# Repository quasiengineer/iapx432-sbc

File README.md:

# System board for Intel APX 432 GDP
FPGA-based single board computer to run iAPX 432 GDP

## Board

Full schematics in [pdf format](./images/schematic.pdf)

Here is shown only FPGA part of the board:

Archive with gerber files and drill locations could be found [here](./pcb/manufacturing.zip)

Bill of material in [CSV format](./pcb/bom.csv)

| Reference                                                                                                                                                                      | Qty | Value                   | Mouser Part Number   |
|---|---|---|---|
| Y1                                                                                                                                                                             | 1   | 250Mhz                  | 972-XLH536250000000I |
| U1                                                                                                                                                                             | 1   | SRAM                    | 870-61LPS12836A5TQL  |
| U2                                                                                                                                                                             | 1   | ICE40                   | 842-ICE40HX4K-TQ144  |
| FB1                                                                                                                                                                            | 1   | Ferrite_Bead            | 81-BLM18BD152SH1D    |
| D1                                                                                                                                                                             | 1   | Red                     | 710-150080RS75000    |
| D3,D4                                                                                                                                                                          | 2   | Green                   | 710-150080GS75000    |
| J1                                                                                                                                                                             | 1   | Type-C                  | 656-DX07S016JA1R1500 |
| L1                                                                                                                                                                             | 1   | 1u5, 5A                 | 652-SRP6530A-1R5M    |
| L2,L3                                                                                                                                                                          | 2   | 0u68, 5.5A              | 652-SRP2512-R68M     |
| J3                                                                                                                                                                             | 1   | Power                   | 649-67997-200HLF     |
| J2                                                                                                                                                                             | 1   | FPGA programming / UART | 649-1012938190604BLF |
| SW1                                                                                                                                                                            | 1   | FPGA Reset              | 640-SWT0010015016SSA |
| Q1                                                                                                                                                                             | 1   | MMBT3904                | 637-MMBT3904         |
| D2                                                                                                                                                                             | 1   | 1N5819                  | 621-1N5819HW-F       |
| R11,R12,R13,R14,R19                                                                                                                                                            | 5   | 100k                    | 603-RT0805DRE07100KL |
| R23                                                                                                                                                                            | 1   | 470R                    | 603-RT0805BRD07470RL |
| R21,R22                                                                                                                                                                        | 2   | 5k1                     | 603-RC0805FR-075K1L  |
| R2,R18                                                                                                                                                                         | 2   | 4k7                     | 603-RC0805FR-074K7L  |
| R16                                                                                                                                                                            | 1   | 34k8                    | 603-RC0805FR-0734K8L |
| R17,R20                                                                                                                                                                        | 2   | 2k2                     | 603-RC0805FR-072K2L  |
| R15                                                                                                                                                                            | 1   | 158k                    | 603-RC0805FR-07158KL |
| R1                                                                                                                                                                             | 1   | 22R                     | 603-RC0805FR-1322RL  |
| C43                                                                                                                                                                            | 1   | 33p                     | 603-CC805KRNPO9BN330 |
| C42                                                                                                                                                                            | 1   | 22p                     | 603-CC805JRNPO9BN220 |
| R9,R10                                                                                                                                                                         | 2   | 10                      | 603-AF0805FR-0710RL  |
| R4,R5,R8                                                                                                                                                                       | 3   | 100R                    | 603-AC0805FR-13100RL |
| R3,R6,R7                                                                                                                                                                       | 3   | 10k                     | 603-AA0805FR-0710KL  |
| U6                                                                                                                                                                             | 1   | TPS63002                | 595-TPS63002DRCR     |
| IC3                                                                                                                                                                            | 1   | Control signals         | 595-LVC16T245DGVRG4  |
| IC1                                                                                                                                                                            | 1   | Address/data bus        | 595-LVC16T245DGVRG4  |
| U4,U5                                                                                                                                                                          | 2   | LX7167ACLD-TR           | 494-LX7167ACLD-TR    |
| U3                                                                                                                                                                             | 1   | Bitstream flash         | 454-W25Q16JVSSIQ     |
| C38,C39,C46,C47                                                                                                                                                                | 4   | 1u                      | 187-CL21B105KPFNNNE  |
| C29,C30,C32,C33,C44,C45                                                                                                                                                        | 6   | 22u                     | 187-CL21A226MAYNNNE  |
| C34,C40,C41                                                                                                                                                                    | 3   | 10u                     | 187-CL21A106KQFNNNG  |
| C1..C19,C21,C22,C23,C25..C28,C31,C35,C36,C37,C50..C65 | 46  | 100n                    | 187-CL10B104KB8NNNC  |
| U8                                                                                                                                                                             | 1   | 43202                   |                      |
| U7                                                                                                                                                                             | 1   | 43201                   |                      |

## FPGA bitstream

Here is compiled [bitsream](./gateware/build/iapx432-sbc.bin).
You can flash it to memory chip via SPI programmer (there is 6-pin header for that).

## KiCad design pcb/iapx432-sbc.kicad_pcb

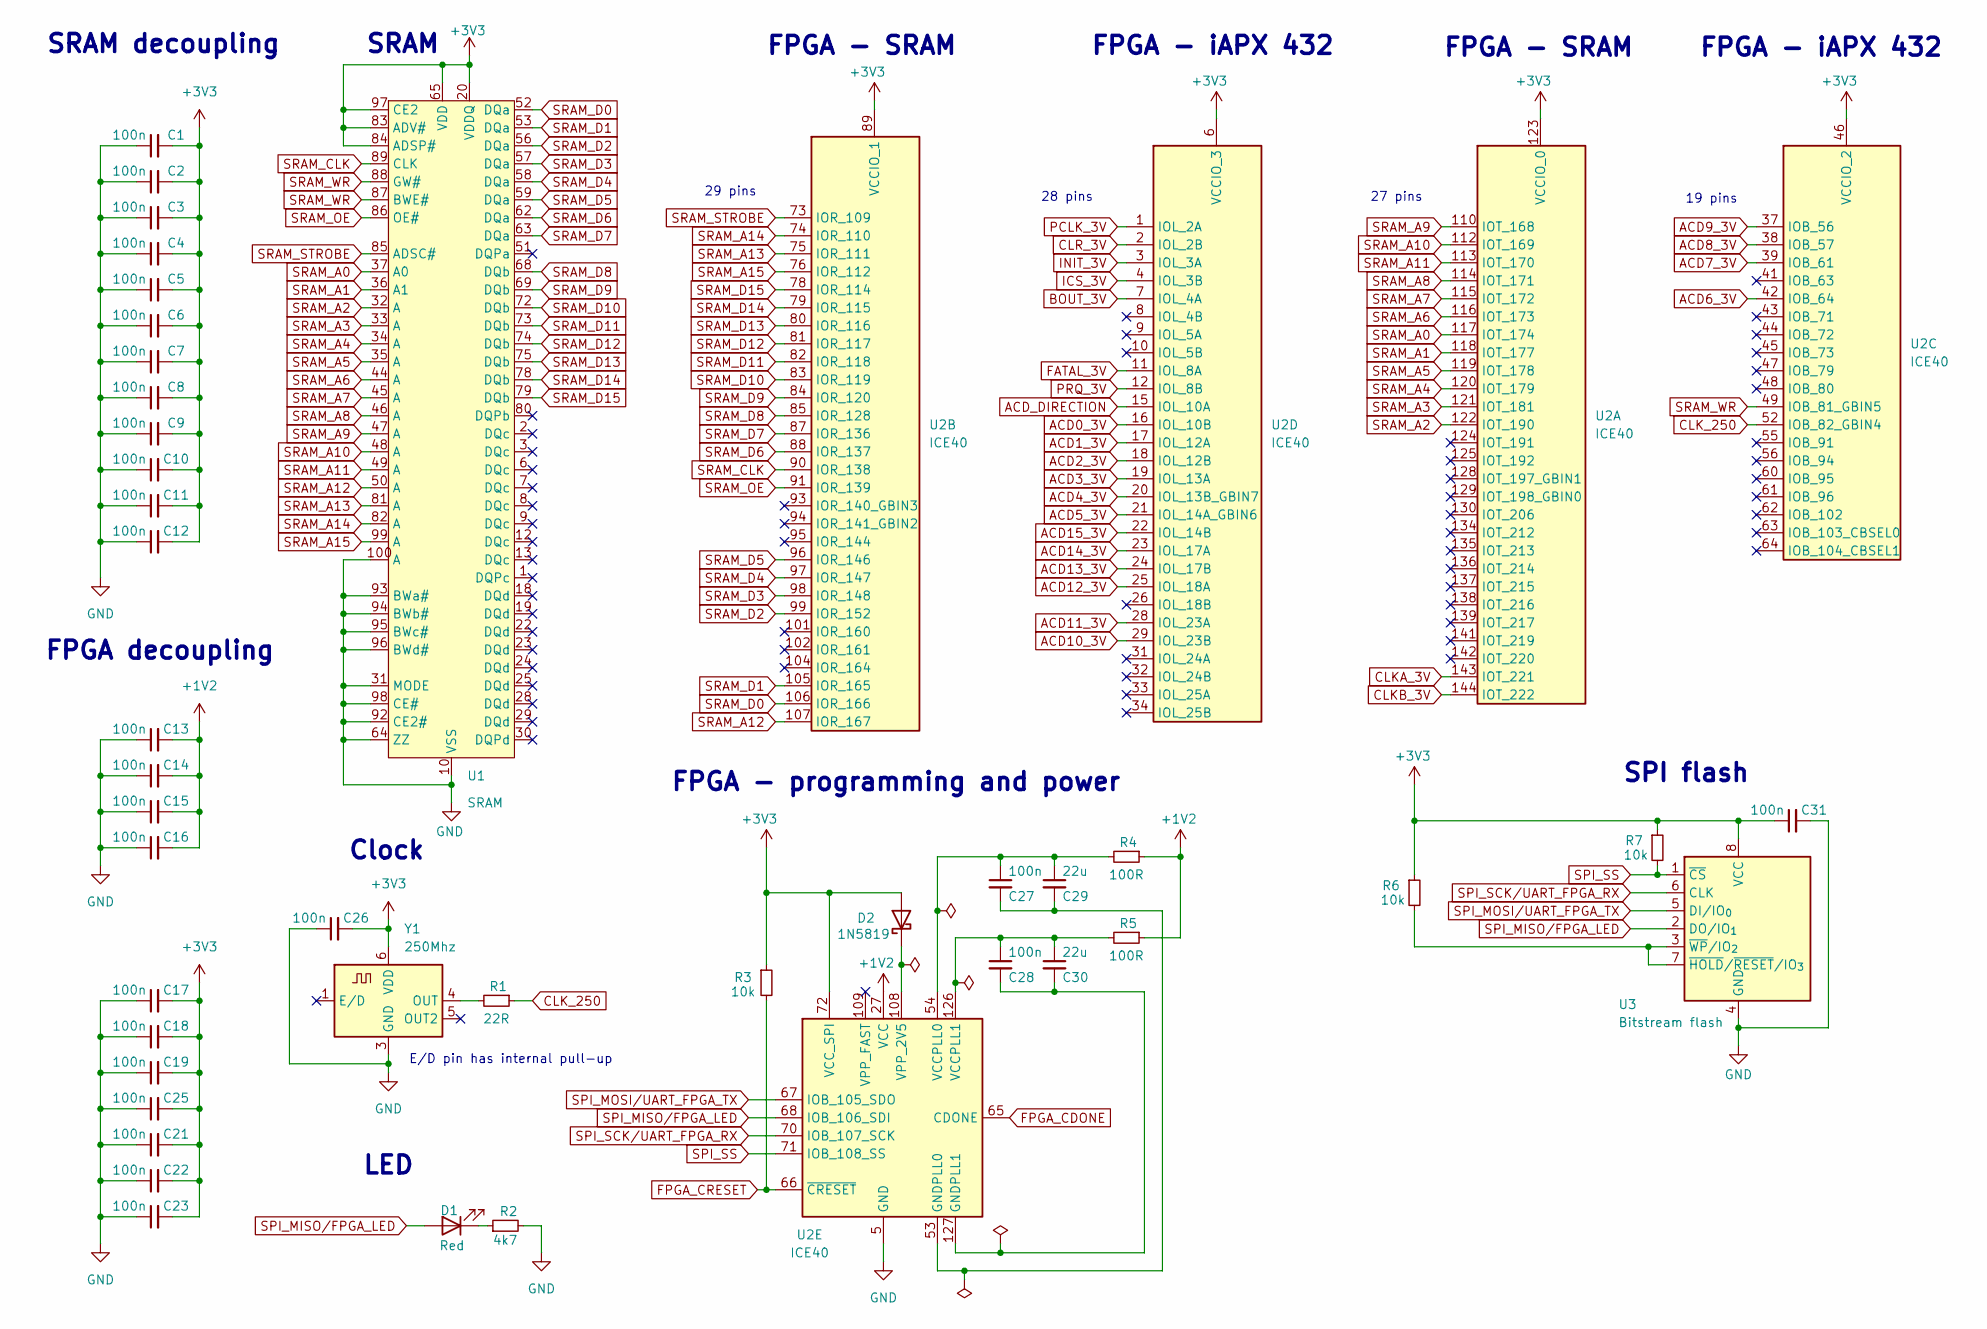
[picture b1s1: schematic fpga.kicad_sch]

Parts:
C1, C2, C3, C4, C5, C6, C7, C8, C9, C10, C11, C12, C13, C14, C15, C16, C17, C18, C19, C21, C22, C23, C25, C26, C27, C28, C31: 100n; C_0603_1608Metric_Pad1.08x0.95mm_HandSolder; Mouser Part Number 187-CL10B104KB8NNNC
C29, C30: 22u; C_0805_2012Metric_Pad1.18x1.45mm_HandSolder; Mouser Part Number 187-CL21A226MAYNNNE
D1: Red; LED_0805_2012Metric_Pad1.15x1.40mm_HandSolder; Mouser Part Number 710-150080RS75000
D2: 1N5819; D_SOD-123; Mouser Part Number 621-1N5819HW-F
R1: 22R; R_0805_2012Metric_Pad1.20x1.40mm_HandSolder; Mouser Part Number 603-RC0805FR-1322RL
R2: 4k7; R_0805_2012Metric_Pad1.20x1.40mm_HandSolder; Mouser Part Number 603-RC0805FR-074K7L
R3, R6, R7: 10k; R_0805_2012Metric_Pad1.20x1.40mm_HandSolder; Mouser Part Number 603-AA0805FR-0710KL
R4, R5: 100R; R_0805_2012Metric_Pad1.20x1.40mm_HandSolder; Mouser Part Number 603-AC0805FR-13100RL
U1: SRAM; PQFP-100_14x20mm_P0.65mm; Mouser Part Number 870-61LPS12836A5TQL
U2: ICE40; TQFP-144_20x20mm_P0.5mm; Mouser Part Number 842-ICE40HX4K-TQ144
U3: Bitstream flash; SOIC-8_5.3x5.3mm_P1.27mm; Mouser Part Number 454-W25Q16JVSSIQ
Y1: 250Mhz; XLH536250.000000I; Mouser Part Number 972-XLH536250000000I

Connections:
+1V2: C13.2, C14.2, C15.2, C16.2, R4.1, R5.1, U2.27 (VCC), U2.40 (VCC), U2.92 (VCC), U2.111 (VCC); also elsewhere on the board
+3V3: C1.2, C2.2, C3.2, C4.2, C5.2, C6.2, C7.2, C8.2, C9.2, C10.2, C11.2, C12.2, C17.2, C18.2, C19.2, C21.2, C22.2, C23.2, C25.2, C26.2, C31.1, D2.2 (A), R3.1, R6.1, R7.1, U1.4 (VDDQ), U1.11 (VDDQ), U1.15 (VDD), U1.20 (VDDQ), U1.27 (VDDQ), U1.41 (VDD), U1.54 (VDDQ), U1.61 (VDDQ), U1.65 (VDD), U1.70 (VDDQ), U1.77 (VDDQ), U1.83 (ADV#), U1.84 (ADSP#), U1.91 (VDD), U1.97 (CE2), U2.6 (VCCIO_3), U2.30 (VCCIO_3), U2.46 (VCCIO_2), U2.57 (VCCIO_2), U2.72 (VCC_SPI), U2.89 (VCCIO_1), U2.100 (VCCIO_1), U2.123 (VCCIO_0), U2.131 (VCCIO_0), U3.8 (VCC), Y1.6 (VDD); also elsewhere on the board
ACD0_3V: U2.16 (IOL_10B); also elsewhere on the board
ACD1_3V: U2.17 (IOL_12A); also elsewhere on the board
ACD2_3V: U2.18 (IOL_12B); also elsewhere on the board
ACD3_3V: U2.19 (IOL_13A); also elsewhere on the board
ACD4_3V: U2.20 (IOL_13B_GBIN7); also elsewhere on the board
ACD5_3V: U2.21 (IOL_14A_GBIN6); also elsewhere on the board
ACD6_3V: U2.42 (IOB_64); also elsewhere on the board
ACD7_3V: U2.39 (IOB_61); also elsewhere on the board
ACD8_3V: U2.38 (IOB_57); also elsewhere on the board
ACD9_3V: U2.37 (IOB_56); also elsewhere on the board
ACD10_3V: U2.29 (IOL_23B); also elsewhere on the board
ACD11_3V: U2.28 (IOL_23A); also elsewhere on the board
ACD12_3V: U2.25 (IOL_18A); also elsewhere on the board
ACD13_3V: U2.24 (IOL_17B); also elsewhere on the board
ACD14_3V: U2.23 (IOL_17A); also elsewhere on the board
ACD15_3V: U2.22 (IOL_14B); also elsewhere on the board
ACD_DIRECTION: U2.15 (IOL_10A); also elsewhere on the board
BOUT_3V: U2.7 (IOL_4A); also elsewhere on the board
CLKA_3V: U2.143 (IOT_221); also elsewhere on the board
CLKB_3V: U2.144 (IOT_222); also elsewhere on the board
CLK_250: R1.1, U2.52 (IOB_82_GBIN4)
CLR_3V: U2.2 (IOL_2B); also elsewhere on the board
FATAL_3V: U2.11 (IOL_8A); also elsewhere on the board
FPGA_CDONE: U2.65 (CDONE); also elsewhere on the board
FPGA_CRESET: R3.2, U2.66 (~CRESET); also elsewhere on the board
GND: C1.1, C2.1, C3.1, C4.1, C5.1, C6.1, C7.1, C8.1, C9.1, C10.1, C11.1, C12.1, C13.1, C14.1, C15.1, C16.1, C17.1, C18.1, C19.1, C21.1, C22.1, C23.1, C25.1, C26.1, C31.2, R2.2, U1.5 (VSS), U1.10 (VSS), U1.17 (VSS), U1.21 (VSS), U1.26 (VSS), U1.31 (MODE), U1.40 (VSS), U1.55 (VSS), U1.60 (VSS), U1.64 (ZZ), U1.67 (VSS), U1.71 (VSS), U1.76 (VSS), U1.90 (VSS), U1.92 (CE2#), U1.93 (BWa#), U1.94 (BWb#), U1.95 (BWc#), U1.96 (BWd#), U1.98 (CE#), U1.100 (A), U2.5 (GND), U2.13 (GND), U2.14 (GND), U2.59 (GND), U2.69 (GND), U2.86 (GND), U2.103 (GND), U2.132 (GND), U2.140 (GND), U3.4 (GND), Y1.3 (GND); also elsewhere on the board
ICS_3V: U2.4 (IOL_3B); also elsewhere on the board
INIT_3V: U2.3 (IOL_3A); also elsewhere on the board
unnamed: D1.1 (K), R2.1
unnamed: D2.1 (K), U2.108 (VPP_2V5)
unnamed: C27.2, C29.2, U2.53 (GNDPLL0)
unnamed: C28.2, C30.2, U2.127 (GNDPLL1)
unnamed: C27.1, C29.1, R4.2, U2.54 (VCCPLL0)
unnamed: C28.1, C30.1, R5.2, U2.126 (VCCPLL1)
unnamed: R6.2, U3.3 (~WP/IO_{2}), U3.7 (~HOLD/~RESET/IO_{3})
unnamed: R1.2, Y1.4 (OUT)
PCLK_3V: U2.1 (IOL_2A); also elsewhere on the board
PRQ_3V: U2.12 (IOL_8B); also elsewhere on the board
SPI_MISO/FPGA_LED: D1.2 (A), U2.68 (IOB_106_SDI), U3.2 (DO/IO_{1}); also elsewhere on the board
SPI_MOSI/UART_FPGA_TX: U2.67 (IOB_105_SDO), U3.5 (DI/IO_{0}); also elsewhere on the board
SPI_SCK/UART_FPGA_RX: U2.70 (IOB_107_SCK), U3.6 (CLK); also elsewhere on the board
SPI_SS: R7.2, U2.71 (IOB_108_SS), U3.1 (~CS); also elsewhere on the board
SRAM_A0: U1.37 (A0), U2.117 (IOT_174)
SRAM_A1: U1.36 (A1), U2.118 (IOT_177)
SRAM_A2: U1.32 (A), U2.122 (IOT_190)
SRAM_A3: U1.33 (A), U2.121 (IOT_181)
SRAM_A4: U1.34 (A), U2.120 (IOT_179)
SRAM_A5: U1.35 (A), U2.119 (IOT_178)
SRAM_A6: U1.44 (A), U2.116 (IOT_173)
SRAM_A7: U1.45 (A), U2.115 (IOT_172)
SRAM_A8: U1.46 (A), U2.114 (IOT_171)
SRAM_A9: U1.47 (A), U2.110 (IOT_168)
SRAM_A10: U1.48 (A), U2.112 (IOT_169)
SRAM_A11: U1.49 (A), U2.113 (IOT_170)
SRAM_A12: U1.50 (A), U2.107 (IOR_167)
SRAM_A13: U1.81 (A), U2.75 (IOR_111)
SRAM_A14: U1.82 (A), U2.74 (IOR_110)
SRAM_A15: U1.99 (A), U2.76 (IOR_112)
SRAM_CLK: U1.89 (CLK), U2.90 (IOR_138)
SRAM_D0: U1.52 (DQa), U2.106 (IOR_166)
SRAM_D1: U1.53 (DQa), U2.105 (IOR_165)
SRAM_D2: U1.56 (DQa), U2.99 (IOR_152)
SRAM_D3: U1.57 (DQa), U2.98 (IOR_148)
SRAM_D4: U1.58 (DQa), U2.97 (IOR_147)
SRAM_D5: U1.59 (DQa), U2.96 (IOR_146)
SRAM_D6: U1.62 (DQa), U2.88 (IOR_137)
SRAM_D7: U1.63 (DQa), U2.87 (IOR_136)
SRAM_D8: U1.68 (DQb), U2.85 (IOR_128)
SRAM_D9: U1.69 (DQb), U2.84 (IOR_120)
SRAM_D10: U1.72 (DQb), U2.83 (IOR_119)
SRAM_D11: U1.73 (DQb), U2.82 (IOR_118)
SRAM_D12: U1.74 (DQb), U2.81 (IOR_117)
SRAM_D13: U1.75 (DQb), U2.80 (IOR_116)
SRAM_D14: U1.78 (DQb), U2.79 (IOR_115)
SRAM_D15: U1.79 (DQb), U2.78 (IOR_114)
SRAM_OE: U1.86 (OE#), U2.91 (IOR_139)
SRAM_STROBE: U1.85 (ADSC#), U2.73 (IOR_109)
SRAM_WR: U1.87 (BWE#), U1.88 (GW#), U2.49 (IOB_81_GBIN5)

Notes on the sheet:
Clock
SRAM
FPGA decoupling
FPGA - SRAM
FPGA - iAPX 432
28 pins
19 pins
27 pins
FPGA - programming and power
E/D pin has internal pull-up
SRAM decoupling
SPI flash
LED
29 pins

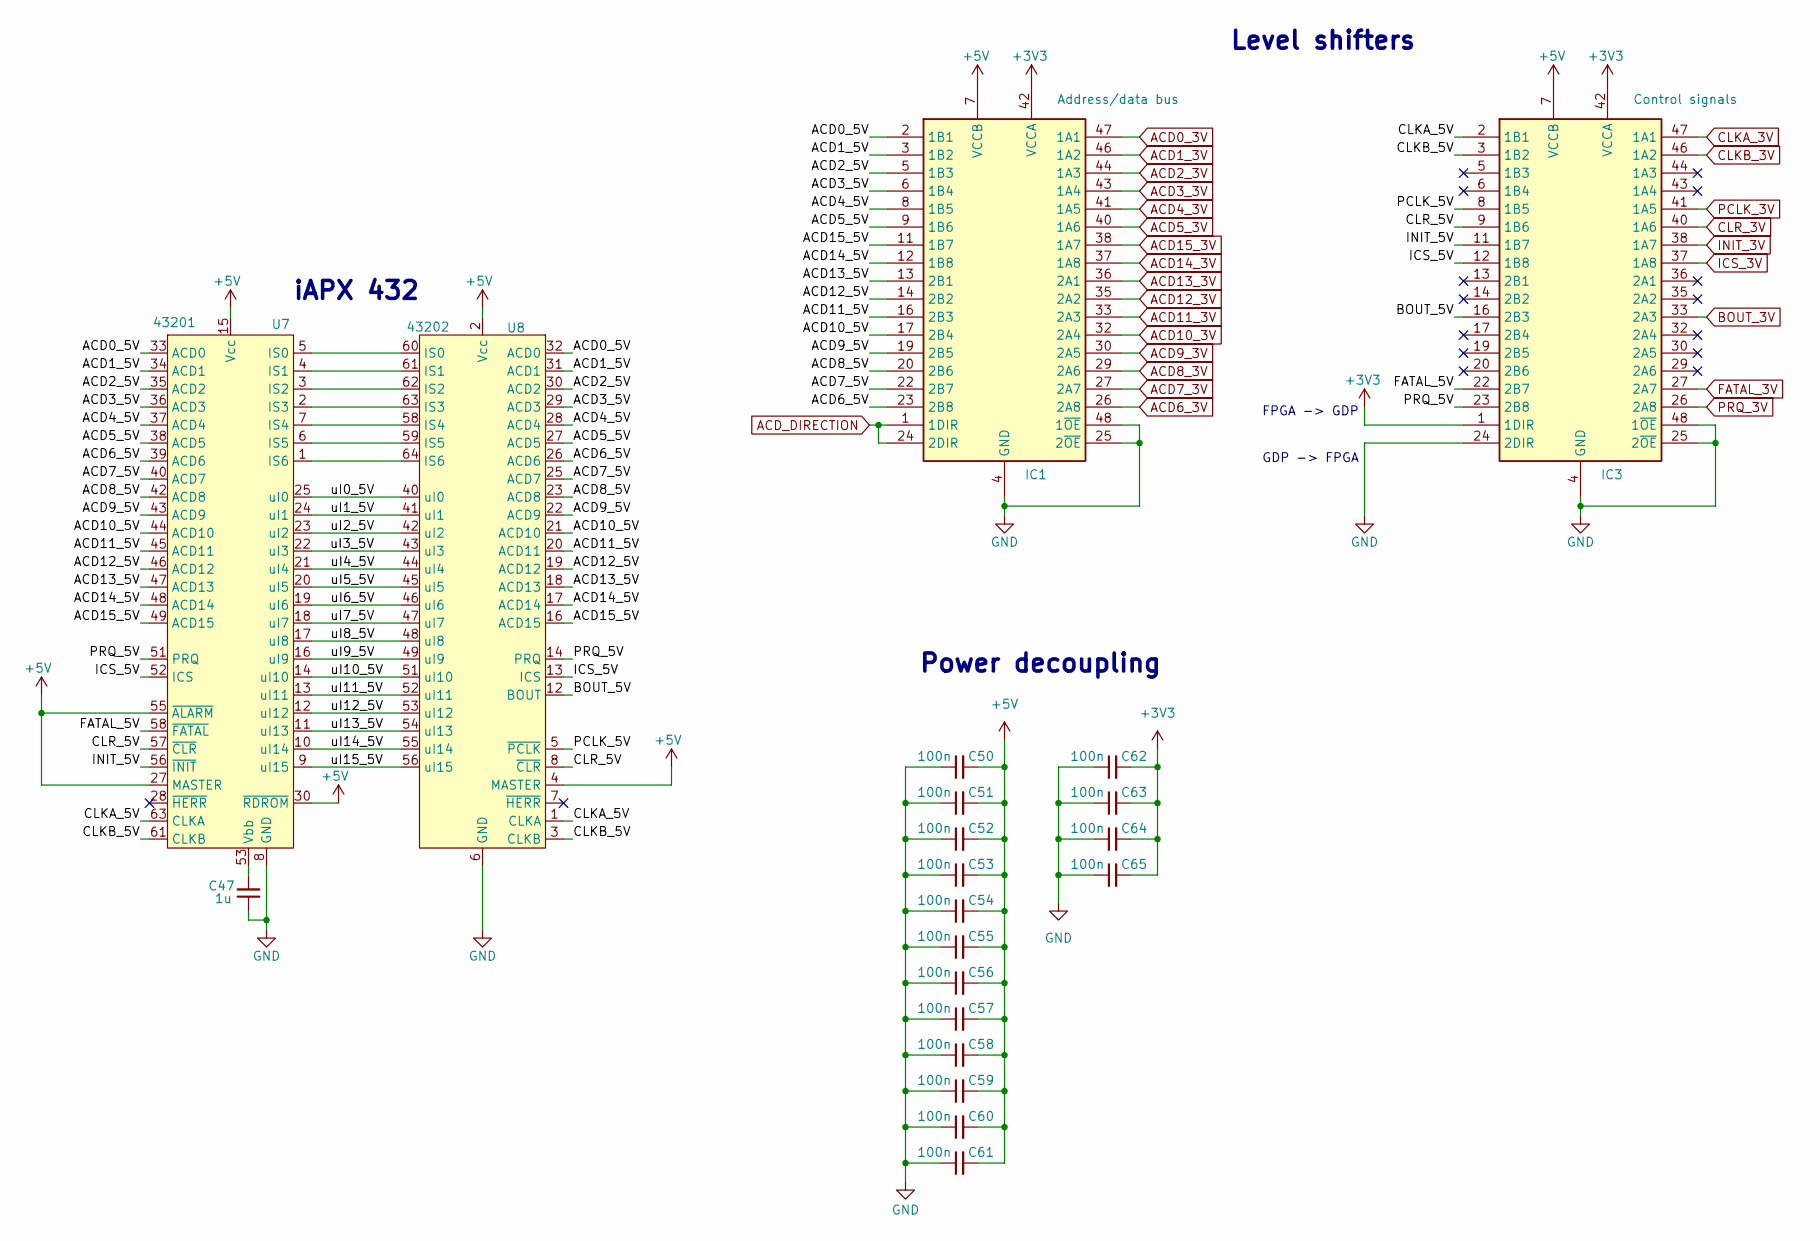
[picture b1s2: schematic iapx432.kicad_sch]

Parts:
C47: 1u; C_0805_2012Metric_Pad1.18x1.45mm_HandSolder; Mouser Part Number 187-CL21B105KPFNNNE
C50, C51, C52, C53, C54, C55, C56, C57, C58, C59, C60, C61, C62, C63, C64, C65: 100n; C_0603_1608Metric_Pad1.08x0.95mm_HandSolder; Mouser Part Number 187-CL10B104KB8NNNC
IC1: Address/data bus; TSSOP-48_4.4x9.7mm_P0.4mm; Mouser Part Number 595-LVC16T245DGVRG4
IC3: Control signals; TSSOP-48_4.4x9.7mm_P0.4mm; Mouser Part Number 595-LVC16T245DGVRG4
U7: 43201; 3M_QUIP64
U8: 43202; 3M_QUIP64

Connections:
+3V3: C62.2, C63.2, C64.2, C65.2, IC1.31 (VCCA), IC1.42 (VCCA), IC3.1 (1DIR), IC3.31 (VCCA), IC3.42 (VCCA); also elsewhere on the board
+5V: C50.2, C51.2, C52.2, C53.2, C54.2, C55.2, C56.2, C57.2, C58.2, C59.2, C60.2, C61.2, IC1.7 (VCCB), IC1.18 (VCCB), IC3.7 (VCCB), IC3.18 (VCCB), U7.15 (Vcc), U7.27 (MASTER), U7.30 (~RDROM), U7.32 (Vcc), U7.50 (Vcc), U7.55 (~ALARM), U7.62 (Vcc), U8.2 (Vcc), U8.4 (MASTER), U8.15 (Vcc), U8.38 (Vcc), U8.50 (Vcc); also elsewhere on the board
/iapx432/ACD0_5V: IC1.2 (1B1), U7.33 (ACD0), U8.32 (ACD0)
/iapx432/ACD1_5V: IC1.3 (1B2), U7.34 (ACD1), U8.31 (ACD1)
/iapx432/ACD2_5V: IC1.5 (1B3), U7.35 (ACD2), U8.30 (ACD2)
/iapx432/ACD3_5V: IC1.6 (1B4), U7.36 (ACD3), U8.29 (ACD3)
/iapx432/ACD4_5V: IC1.8 (1B5), U7.37 (ACD4), U8.28 (ACD4)
/iapx432/ACD5_5V: IC1.9 (1B6), U7.38 (ACD5), U8.27 (ACD5)
/iapx432/ACD6_5V: IC1.23 (2B8), U7.39 (ACD6), U8.26 (ACD6)
/iapx432/ACD7_5V: IC1.22 (2B7), U7.40 (ACD7), U8.25 (ACD7)
/iapx432/ACD8_5V: IC1.20 (2B6), U7.42 (ACD8), U8.23 (ACD8)
/iapx432/ACD9_5V: IC1.19 (2B5), U7.43 (ACD9), U8.22 (ACD9)
/iapx432/ACD10_5V: IC1.17 (2B4), U7.44 (ACD10), U8.21 (ACD10)
/iapx432/ACD11_5V: IC1.16 (2B3), U7.45 (ACD11), U8.20 (ACD11)
/iapx432/ACD12_5V: IC1.14 (2B2), U7.46 (ACD12), U8.19 (ACD12)
/iapx432/ACD13_5V: IC1.13 (2B1), U7.47 (ACD13), U8.18 (ACD13)
/iapx432/ACD14_5V: IC1.12 (1B8), U7.48 (ACD14), U8.17 (ACD14)
/iapx432/ACD15_5V: IC1.11 (1B7), U7.49 (ACD15), U8.16 (ACD15)
/iapx432/BOUT_5V: IC3.16 (2B3), U8.12 (BOUT)
/iapx432/CLKA_5V: IC3.2 (1B1), U7.63 (CLKA), U8.1 (CLKA)
/iapx432/CLKB_5V: IC3.3 (1B2), U7.61 (CLKB), U8.3 (CLKB)
/iapx432/CLR_5V: IC3.9 (1B6), U7.57 (~CLR), U8.8 (~CLR)
/iapx432/FATAL_5V: IC3.22 (2B7), U7.58 (~FATAL)
/iapx432/ICS_5V: IC3.12 (1B8), U7.52 (ICS), U8.13 (ICS)
/iapx432/INIT_5V: IC3.11 (1B7), U7.56 (~INIT)
/iapx432/PCLK_5V: IC3.8 (1B5), U8.5 (~PCLK)
/iapx432/PRQ_5V: IC3.23 (2B8), U7.51 (PRQ), U8.14 (PRQ)
/iapx432/uI0_5V: U7.25 (uI0), U8.40 (uI0)
/iapx432/uI1_5V: U7.24 (uI1), U8.41 (uI1)
/iapx432/uI2_5V: U7.23 (uI2), U8.42 (uI2)
/iapx432/uI3_5V: U7.22 (uI3), U8.43 (uI3)
/iapx432/uI4_5V: U7.21 (uI4), U8.44 (uI4)
/iapx432/uI5_5V: U7.20 (uI5), U8.45 (uI5)
/iapx432/uI6_5V: U7.19 (uI6), U8.46 (uI6)
/iapx432/uI7_5V: U7.18 (uI7), U8.47 (uI7)
/iapx432/uI8_5V: U7.17 (uI8), U8.48 (uI8)
/iapx432/uI9_5V: U7.16 (uI9), U8.49 (uI9)
/iapx432/uI10_5V: U7.14 (uI10), U8.51 (uI10)
/iapx432/uI11_5V: U7.13 (uI11), U8.52 (uI11)
/iapx432/uI12_5V: U7.12 (uI12), U8.53 (uI12)
/iapx432/uI13_5V: U7.11 (uI13), U8.54 (uI13)
/iapx432/uI14_5V: U7.10 (uI14), U8.55 (uI14)
/iapx432/uI15_5V: U7.9 (uI15), U8.56 (uI15)
ACD0_3V: IC1.47 (1A1); also elsewhere on the board
ACD1_3V: IC1.46 (1A2); also elsewhere on the board
ACD2_3V: IC1.44 (1A3); also elsewhere on the board
ACD3_3V: IC1.43 (1A4); also elsewhere on the board
ACD4_3V: IC1.41 (1A5); also elsewhere on the board
ACD5_3V: IC1.40 (1A6); also elsewhere on the board
ACD6_3V: IC1.26 (2A8); also elsewhere on the board
ACD7_3V: IC1.27 (2A7); also elsewhere on the board
ACD8_3V: IC1.29 (2A6); also elsewhere on the board
ACD9_3V: IC1.30 (2A5); also elsewhere on the board
ACD10_3V: IC1.32 (2A4); also elsewhere on the board
ACD11_3V: IC1.33 (2A3); also elsewhere on the board
ACD12_3V: IC1.35 (2A2); also elsewhere on the board
ACD13_3V: IC1.36 (2A1); also elsewhere on the board
ACD14_3V: IC1.37 (1A8); also elsewhere on the board
ACD15_3V: IC1.38 (1A7); also elsewhere on the board
ACD_DIRECTION: IC1.1 (1DIR), IC1.24 (2DIR); also elsewhere on the board
BOUT_3V: IC3.33 (2A3); also elsewhere on the board
CLKA_3V: IC3.47 (1A1); also elsewhere on the board
CLKB_3V: IC3.46 (1A2); also elsewhere on the board
CLR_3V: IC3.40 (1A6); also elsewhere on the board
FATAL_3V: IC3.27 (2A7); also elsewhere on the board
GND: C47.1, C50.1, C51.1, C52.1, C53.1, C54.1, C55.1, C56.1, C57.1, C58.1, C59.1, C60.1, C61.1, C62.1, C63.1, C64.1, C65.1, IC1.4 (GND), IC1.10 (GND), IC1.15 (GND), IC1.21 (GND), IC1.25 (2~OE), IC1.28 (GND), IC1.34 (GND), IC1.39 (GND), IC1.45 (GND), IC1.48 (1~OE), IC3.4 (GND), IC3.10 (GND), IC3.15 (GND), IC3.21 (GND), IC3.24 (2DIR), IC3.25 (2~OE), IC3.28 (GND), IC3.34 (GND), IC3.39 (GND), IC3.45 (GND), IC3.48 (1~OE), U7.8 (GND), U7.26 (GND), U7.41 (GND), U7.60 (GND), U7.64 (GND), U8.6 (GND), U8.24 (GND), U8.35 (GND), U8.39 (GND), U8.57 (GND); also elsewhere on the board
ICS_3V: IC3.37 (1A8); also elsewhere on the board
INIT_3V: IC3.38 (1A7); also elsewhere on the board
unnamed: U7.5 (IS0), U8.60 (IS0)
unnamed: U7.4 (IS1), U8.61 (IS1)
unnamed: U7.3 (IS2), U8.62 (IS2)
unnamed: U7.2 (IS3), U8.63 (IS3)
unnamed: U7.7 (IS4), U8.58 (IS4)
unnamed: U7.6 (IS5), U8.59 (IS5)
unnamed: U7.1 (IS6), U8.64 (IS6)
unnamed: C47.2, U7.53 (Vbb)
PCLK_3V: IC3.41 (1A5); also elsewhere on the board
PRQ_3V: IC3.26 (2A8); also elsewhere on the board

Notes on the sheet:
iAPX 432
Level shifters
FPGA -> GDP
GDP -> FPGA
Power decoupling

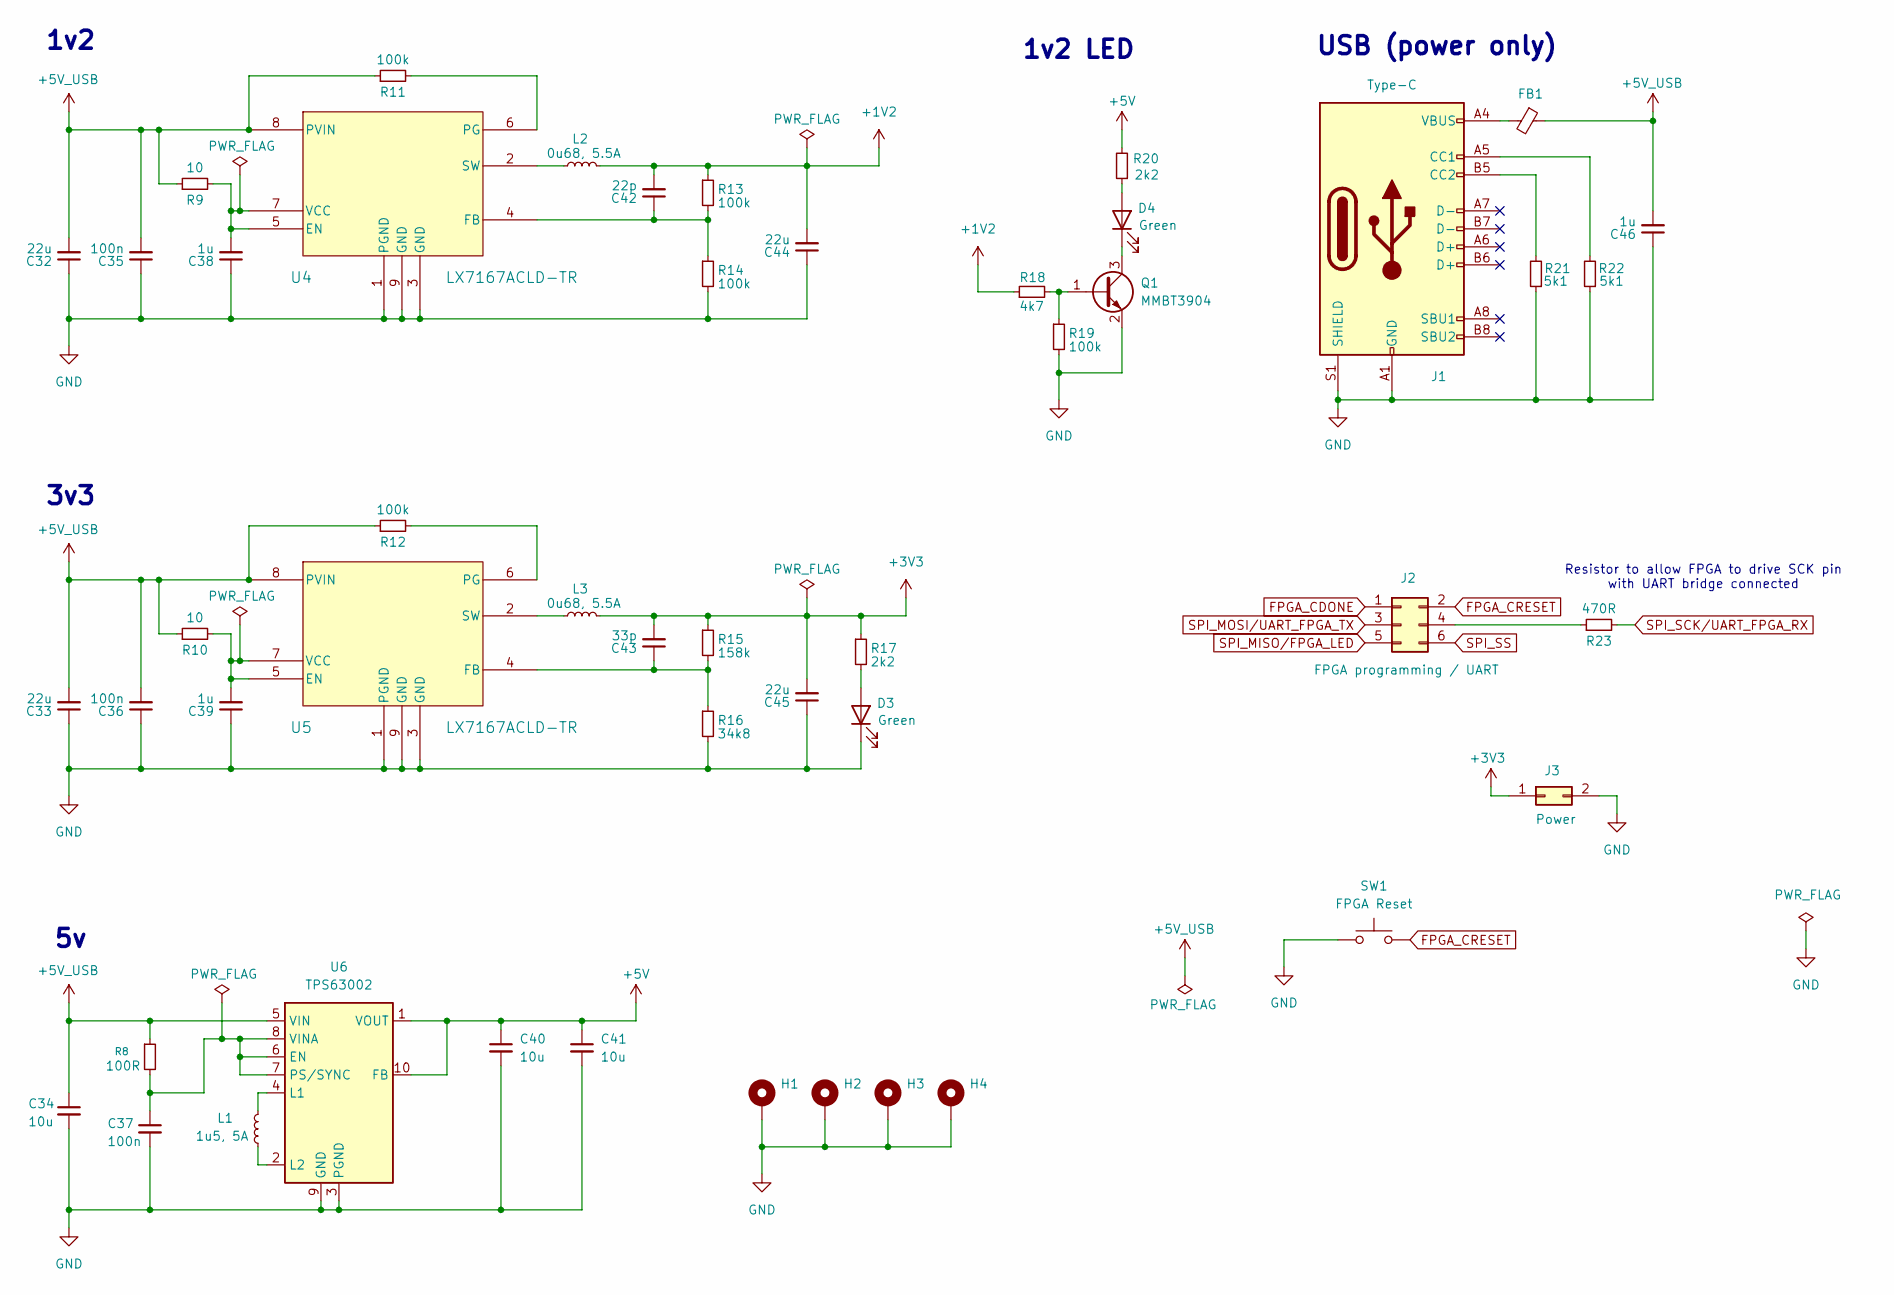
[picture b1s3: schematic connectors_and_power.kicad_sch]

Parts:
C32, C33, C44, C45: 22u; C_0805_2012Metric_Pad1.18x1.45mm_HandSolder; Mouser Part Number 187-CL21A226MAYNNNE
C34, C40, C41: 10u; C_0805_2012Metric_Pad1.18x1.45mm_HandSolder; Mouser Part Number 187-CL21A106KQFNNNG
C35, C36, C37: 100n; C_0603_1608Metric_Pad1.08x0.95mm_HandSolder; Mouser Part Number 187-CL10B104KB8NNNC
C38, C39, C46: 1u; C_0805_2012Metric_Pad1.18x1.45mm_HandSolder; Mouser Part Number 187-CL21B105KPFNNNE
C42: 22p; C_0805_2012Metric_Pad1.18x1.45mm_HandSolder; Mouser Part Number 603-CC805JRNPO9BN220
C43: 33p; C_0805_2012Metric_Pad1.18x1.45mm_HandSolder; Mouser Part Number 603-CC805KRNPO9BN330
D3, D4: Green; LED_0805_2012Metric_Pad1.15x1.40mm_HandSolder; Mouser Part Number 710-150080GS75000
FB1: Ferrite_Bead; L_0603_1608Metric_Pad1.05x0.95mm_HandSolder; Mouser Part Number 81-BLM18BD152SH1D
H1, H2, H3, H4: MountingHole_Pad; MountingHole_2.2mm_M2_Pad_Via
J1: Type-C; USB_C_Receptacle_JAE_DX07S016JA1R1500; Mouser Part Number 656-DX07S016JA1R1500
J2: FPGA programming / UART; PinHeader_2x03_P2.54mm_Vertical; Mouser Part Number 649-1012938190604BLF
J3: Power; PinHeader_1x02_P2.54mm_Vertical; Mouser Part Number 649-67997-200HLF
L1: 1u5, 5A; SRP6530A-1R5M; Mouser Part Number 652-SRP6530A-1R5M
L2, L3: 0u68, 5.5A; L_1008_2520Metric_Pad1.43x2.20mm_HandSolder; Mouser Part Number 652-SRP2512-R68M
Q1: MMBT3904; SOT-23; Mouser Part Number 637-MMBT3904
R8: 100R; R_0805_2012Metric_Pad1.20x1.40mm_HandSolder; Mouser Part Number 603-AC0805FR-13100RL
R9, R10: 10; R_0805_2012Metric_Pad1.20x1.40mm_HandSolder; Mouser Part Number 603-AF0805FR-0710RL
R11, R12, R13, R14, R19: 100k; R_0805_2012Metric_Pad1.20x1.40mm_HandSolder; Mouser Part Number 603-RT0805DRE07100KL
R15: 158k; R_0805_2012Metric_Pad1.20x1.40mm_HandSolder; Mouser Part Number 603-RC0805FR-07158KL
R16: 34k8; R_0805_2012Metric_Pad1.20x1.40mm_HandSolder; Mouser Part Number 603-RC0805FR-0734K8L
R17, R20: 2k2; R_0805_2012Metric_Pad1.20x1.40mm_HandSolder; Mouser Part Number 603-RC0805FR-072K2L
R18: 4k7; R_0805_2012Metric_Pad1.20x1.40mm_HandSolder; Mouser Part Number 603-RC0805FR-074K7L
R21, R22: 5k1; R_0805_2012Metric_Pad1.20x1.40mm_HandSolder; Mouser Part Number 603-RC0805FR-075K1L
R23: 470R; R_0805_2012Metric_Pad1.20x1.40mm_HandSolder; Mouser Part Number 603-RT0805BRD07470RL
SW1: FPGA Reset; SWT0010-015016SSA; Mouser Part Number 640-SWT0010015016SSA
U4, U5: LX7167ACLD-TR; DFN-8-1EP_2x2mm_P0.5mm_EP0.8x1.6mm; Mouser Part Number 494-LX7167ACLD-TR
U6: TPS63002; VSON-10-1EP_3x3mm_P0.5mm_EP1.2x2mm; Mouser Part Number 595-TPS63002DRCR

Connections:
+1V2: C42.2, C44.2, L2.2, R13.1, R18.1; also elsewhere on the board
+3V3: C43.2, C45.2, J3.1, L3.2, R15.1, R17.1; also elsewhere on the board
+5V: C40.1, C41.1, R20.2, U6.1 (VOUT), U6.10 (FB); also elsewhere on the board
+5V_USB: C32.2, C33.2, C34.1, C35.2, C36.2, C46.2, FB1.1, R8.1, R9.1, R10.1, R11.1, R12.1, U4.8 (PVIN), U5.8 (PVIN), U6.5 (VIN)
FPGA_CDONE: J2.1; also elsewhere on the board
FPGA_CRESET: J2.2, SW1.2; also elsewhere on the board
GND: C32.1, C33.1, C34.2, C35.1, C36.1, C37.2, C38.1, C39.1, C40.2, C41.2, C44.1, C45.1, C46.1, D3.1 (K), H1.1, H2.1, H3.1, H4.1, J1.A1 (GND), J1.A12 (GND), J1.B1 (GND), J1.B12 (GND), J1.S1 (SHIELD), J3.2, Q1.2 (E), R14.2, R16.2, R19.2, R21.1, R22.1, SW1.1, U4.1 (PGND), U4.3 (GND), U4.9 (GND), U5.1 (PGND), U5.3 (GND), U5.9 (GND), U6.3 (PGND), U6.9 (GND), U6.11 (PGND); also elsewhere on the board
unnamed: D3.2 (A), R17.2
unnamed: D4.2 (A), R20.1
unnamed: D4.1 (K), Q1.3 (C)
unnamed: FB1.2, J1.A4 (VBUS), J1.A9 (VBUS), J1.B4 (VBUS), J1.B9 (VBUS)
unnamed: J1.A5 (CC1), R22.2
unnamed: J1.B5 (CC2), R21.2
unnamed: J2.4, R23.1
unnamed: Q1.1 (B), R18.2, R19.1
unnamed: C38.2, R9.2, U4.5 (EN), U4.7 (VCC)
unnamed: C42.1, R13.2, R14.1, U4.4 (FB)
unnamed: R11.2, U4.6 (PG)
unnamed: L2.1, U4.2 (SW)
unnamed: C39.2, R10.2, U5.5 (EN), U5.7 (VCC)
unnamed: C43.1, R15.2, R16.1, U5.4 (FB)
unnamed: R12.2, U5.6 (PG)
unnamed: L3.1, U5.2 (SW)
unnamed: C37.1, R8.2, U6.6 (EN), U6.7 (PS/SYNC), U6.8 (VINA)
unnamed: L1.2, U6.4 (L1)
unnamed: L1.1, U6.2 (L2)
SPI_MISO/FPGA_LED: J2.5; also elsewhere on the board
SPI_MOSI/UART_FPGA_TX: J2.3; also elsewhere on the board
SPI_SCK/UART_FPGA_RX: R23.2; also elsewhere on the board
SPI_SS: J2.6; also elsewhere on the board

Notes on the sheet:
1v2 LED
Resistor to allow FPGA to drive SCK pin with UART bridge connected
3v3
1v2
USB (power only)
